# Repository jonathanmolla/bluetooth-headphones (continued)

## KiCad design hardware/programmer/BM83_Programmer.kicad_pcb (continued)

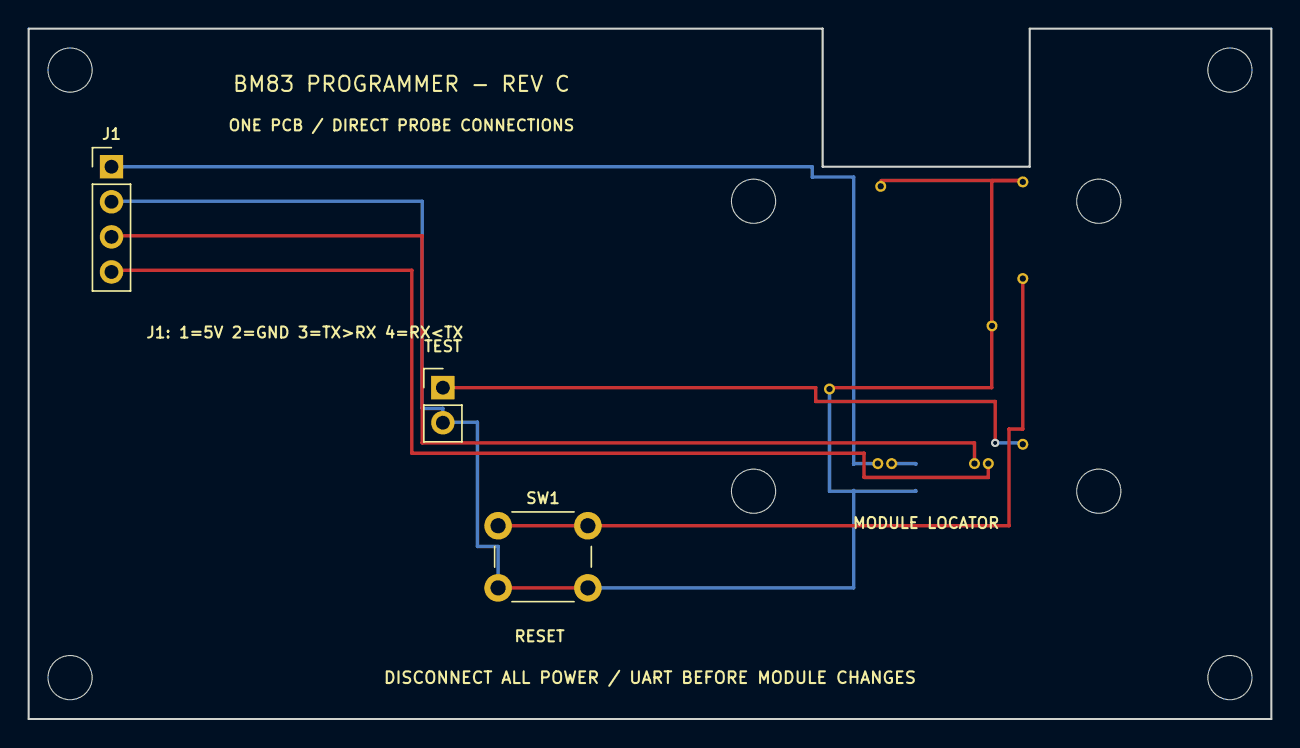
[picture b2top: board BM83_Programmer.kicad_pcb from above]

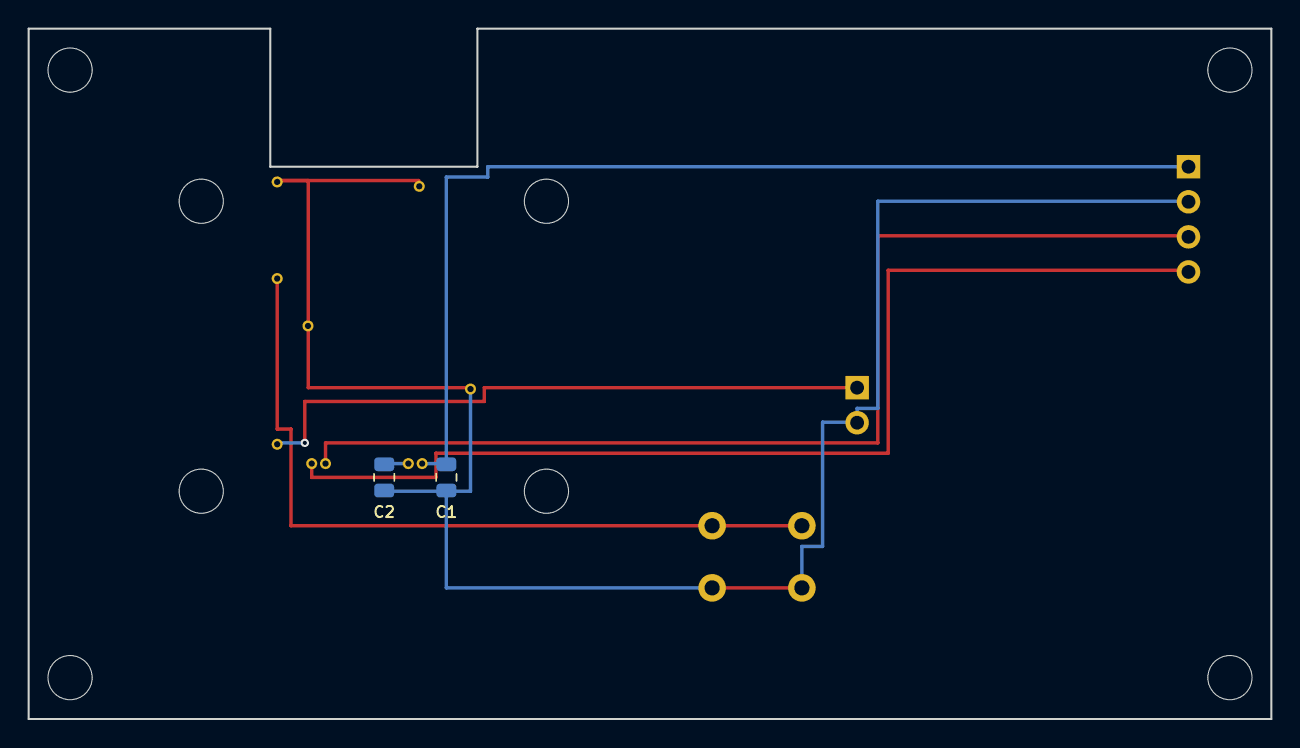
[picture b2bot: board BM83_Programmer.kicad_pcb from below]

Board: 2 copper layers, 90.0 x 50.0 mm, 23 parts (2 on the bottom side), 7 nets.

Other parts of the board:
H1, H2, H3, H4, H5, H6, H7, H8: MountingHole_3.2mm_M3

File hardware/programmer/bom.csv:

Reference,Value,Footprint,Datasheet,Status
C1,1uF / 25V X7R,Capacitor_SMD:C_0805_2012Metric,https://www.murata.com/en-us/products/productdetail?partno=G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,Saved schematic value; see review for pending recommendations
C2,1uF / 25V X7R,Capacitor_SMD:C_0805_2012Metric,https://www.murata.com/en-us/products/productdetail?partno=G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,Saved schematic value; see review for pending recommendations
J1,USB-UART 3V3 LOGIC,Connector_PinHeader_2.54mm:PinHeader_1x04_P2.54mm_Vertical,https://www.samtec.com/products/tsw-104-07-g-s,Saved schematic value; see review for pending recommendations
JP2,TEST MODE,Connector_PinHeader_2.54mm:PinHeader_1x02_P2.54mm_Vertical,https://www.samtec.com/products/tsw-102-07-g-s,Saved schematic value; see review for pending recommendations
P1,BM83 PAD 22,BM83_Programmer:TestPoint_INGUN_GKS080_SolderTail,https://ingun.com/media/01/86/fe/1752238559/INGUN_GKS-080_30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,Saved schematic value; see review for pending recommendations
P2,BM83 PAD 23,BM83_Programmer:TestPoint_INGUN_GKS080_SolderTail,https://ingun.com/media/01/86/fe/1752238559/INGUN_GKS-080_30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,Saved schematic value; see review for pending recommendations
P3,BM83 PAD 29,BM83_Programmer:TestPoint_INGUN_GKS080_SolderTail,https://ingun.com/media/01/86/fe/1752238559/INGUN_GKS-080_30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,Saved schematic value; see review for pending recommendations
P4,BM83 PAD 30,BM83_Programmer:TestPoint_INGUN_GKS080_SolderTail,https://ingun.com/media/01/86/fe/1752238559/INGUN_GKS-080_30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,Saved schematic value; see review for pending recommendations
P5,BM83 PAD 31,BM83_Programmer:TestPoint_INGUN_GKS080_SolderTail,https://ingun.com/media/01/86/fe/1752238559/INGUN_GKS-080_30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,Saved schematic value; see review for pending recommendations
P6,BM83 PAD 43,BM83_Programmer:TestPoint_INGUN_GKS080_SolderTail,https://ingun.com/media/01/86/fe/1752238559/INGUN_GKS-080_30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,Saved schematic value; see review for pending recommendations
P7,BM83 PAD 16,BM83_Programmer:TestPoint_INGUN_GKS080_SolderTail,https://ingun.com/media/01/86/fe/1752238559/INGUN_GKS-080_30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,Saved schematic value; see review for pending recommendations
P8,BM83 PAD 50,BM83_Programmer:TestPoint_INGUN_GKS080_SolderTail,https://ingun.com/media/01/86/fe/1752238559/INGUN_GKS-080_30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,Saved schematic value; see review for pending recommendations
P9,BM83 PAD 56,BM83_Programmer:TestPoint_INGUN_GKS080_SolderTail,https://ingun.com/media/01/86/fe/1752238559/INGUN_GKS-080_30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,Saved schematic value; see review for pending recommendations
P10,BM83 PAD 57,BM83_Programmer:TestPoint_INGUN_GKS080_SolderTail,https://ingun.com/media/01/86/fe/1752238559/INGUN_GKS-080_30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,Saved schematic value; see review for pending recommendations
SW1,RESET,Button_Switch_THT:SW_PUSH_6mm,https://omronfs.omron.com/en_US/ecb/products/pdf/en-b3f.pdf,Saved schematic value; see review for pending recommendations

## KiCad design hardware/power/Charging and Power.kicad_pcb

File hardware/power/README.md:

# Charging and power board

This board contains the USB power input, MCP73833 battery-charging circuit, and TPS7A2030PDBVR 3.0 V regulator.

## Charging and power PCB

**Editable board layout:** [Charging and Power.kicad_pcb](Charging%20and%20Power.kicad_pcb)

**Open the complete KiCad project:** [Charging and Power.kicad_pro](Charging%20and%20Power.kicad_pro)

**View the layout in your browser:** [Charging and power PCB preview](../../docs/images/power-board.svg)

## Schematic and component list

| File | Contents |
| --- | --- |
| [Power schematic](Charging%20and%20Power.kicad_sch) | Charging, regulation, indicators and board connections |
| [Component list](bom.csv) | Schematic references, values, footprints and datasheet links |

[View the power schematic](../../docs/schematics/power/Charging%20and%20Power.svg) · [Open the main audio board](../main/)

## Library files

`MCP73833-AMI_UN.pretty/` and `TPS7A2030PDBVR.pretty/` contain the local charger and regulator CAD assets. Keep these folders and both library tables beside the project when downloading it.

## November 14 review

[Cross-board circuit and layout review](../../docs/design-review-2026-11-14.md) records component values, inter-board pinout, battery/driver selection and reference-design comparisons. The CSV lists schematic parts; the existing Google document remains the purchasing BOM.

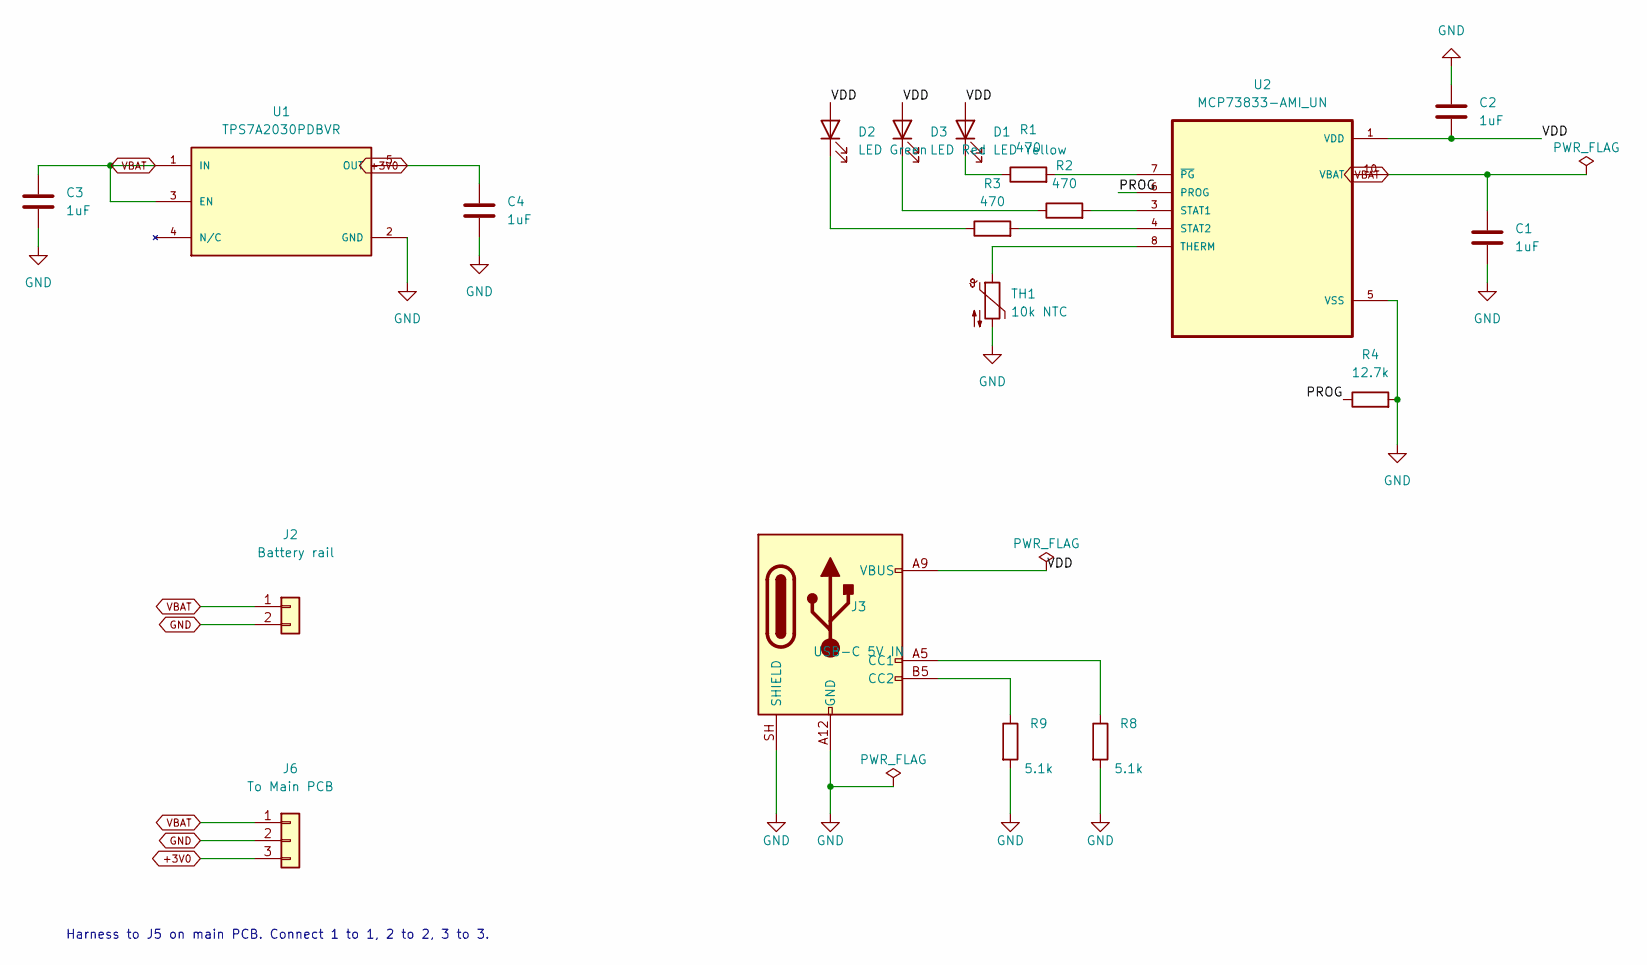
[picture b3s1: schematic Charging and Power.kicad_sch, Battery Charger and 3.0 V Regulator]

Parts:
C1, C2, C3, C4: 1uF; C_0805_2012Metric; MPN GRM219R71E105KA88D
D1: LED Yellow; LED_0805_2012Metric; MPN AP2012SYC
D2: LED Green; LED_0805_2012Metric; MPN AP2012SGC
D3: LED Red; LED_0805_2012Metric; MPN APT2012SURCK
J2: Battery rail; JST_PH_B2B-PH-K_1x02_P2.00mm_Vertical; MPN B2B-PH-K-S(LF)(SN)
J3: USB-C 5V IN; USB_C_Receptacle_GCT_USB4125-xx-x_6P_TopMnt_Horizontal; MPN USB4125-GF-A
J6: To Main PCB; JST_PH_B3B-PH-K_1x03_P2.00mm_Vertical; MPN B3B-PH-K-S(LF)(SN)
R1, R2, R3: 470; R_0805_2012Metric; MPN ERJ-6ENF4700V
R4: 12.7k; R_0603_1608Metric; MPN RC0603FR-0712K7L
R8, R9: 5.1k; R_0805_2012Metric; MPN RC0805FR-075K1L
TH1: 10k NTC; SolderWire-0.1sqmm_1x02_P3.6mm_D0.4mm_OD1mm; MPN B57861S0103F040
U1: TPS7A2030PDBVR; SOT95P280X145-5N; PARTREV H
U2: MCP73833-AMI_UN; SOP50P490X110-10N

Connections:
+3V0: C4.1, J6.3, U1.5 (OUT)
/PROG: R4.1, U2.6 (PROG)
GND: C1.2, C2.1, C3.2, C4.2, J2.2, J3.A12 (GND), J3.B12 (GND), J3.SH (SHIELD), J6.2, R4.2, R8.2, R9.2, TH1.2, U1.2 (GND), U2.5 (VSS)
unnamed: D1.1 (K), R1.1
unnamed: D2.1 (K), R3.1
unnamed: D3.1 (K), R2.1
unnamed: J3.A5 (CC1), R8.1
unnamed: J3.B5 (CC2), R9.1
unnamed: R2.2, U2.3 (STAT1)
unnamed: R3.2, U2.4 (STAT2)
unnamed: TH1.1, U2.8 (THERM)
unnamed: R1.2, U2.7 (~PG)
VBAT: C1.1, C3.1, J2.1, J6.1, U1.1 (IN), U1.3 (EN), U2.9 (VBAT), U2.10 (VBAT)
VDD: C2.2, D1.2 (A), D2.2 (A), D3.2 (A), J3.A9 (VBUS), J3.B9 (VBUS), U2.1 (VDD), U2.2 (VDD)

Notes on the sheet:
Harness to J5 on main PCB. Connect 1 to 1, 2 to 2, 3 to 3.

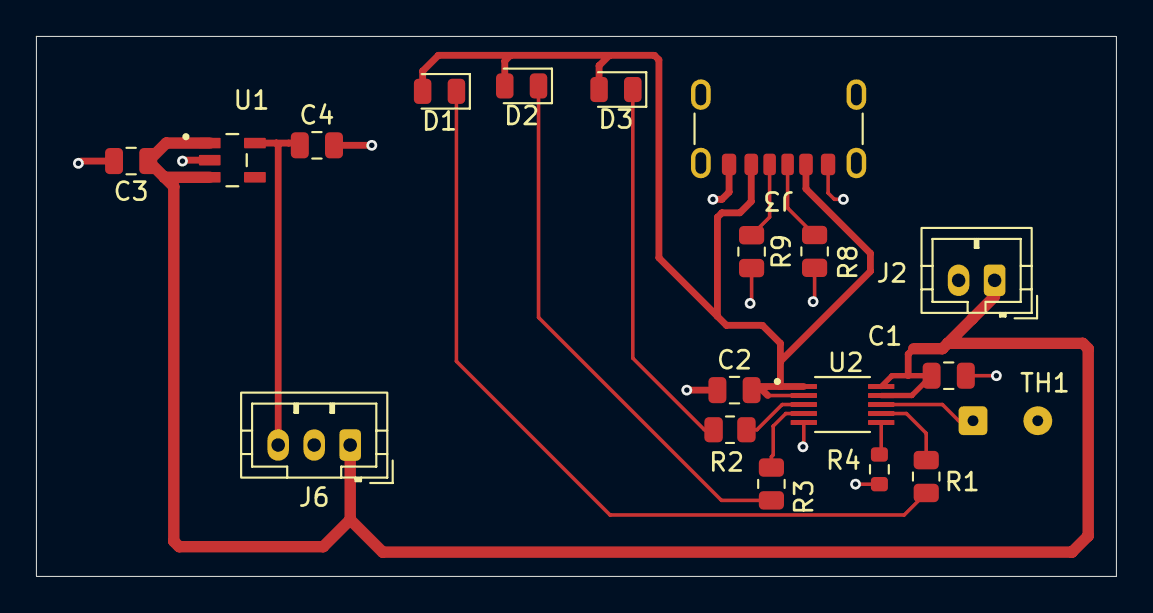
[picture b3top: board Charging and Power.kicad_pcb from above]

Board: 2 copper layers, 60.0 x 30.0 mm, 19 parts (0 on the bottom side), 14 nets.

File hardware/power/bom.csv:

Reference,Value,Footprint,Datasheet,Status
C1,1uF,Capacitor_SMD:C_0805_2012Metric,,Schematic-derived; verify before purchasing
C2,1uF,Capacitor_SMD:C_0805_2012Metric,,Schematic-derived; verify before purchasing
C3,1uF,Capacitor_SMD:C_0805_2012Metric,,Schematic-derived; verify before purchasing
C4,1uF,Capacitor_SMD:C_0805_2012Metric,,Schematic-derived; verify before purchasing
D1,LED Yellow,LED_SMD:LED_0805_2012Metric,,Schematic-derived; verify before purchasing
D2,LED Green,LED_SMD:LED_0805_2012Metric,,Schematic-derived; verify before purchasing
D3,LED Red,LED_SMD:LED_0805_2012Metric,,Schematic-derived; verify before purchasing
J2,Battery rail,Connector_JST:JST_PH_B2B-PH-K_1x02_P2.00mm_Vertical,,Schematic-derived; verify before purchasing
J3,USB-C 5V IN,Connector_USB:USB_C_Receptacle_GCT_USB4125-xx-x_6P_TopMnt_Horizontal,,Schematic-derived; verify before purchasing
J6,To Main PCB,Connector_JST:JST_PH_B3B-PH-K_1x03_P2.00mm_Vertical,,Schematic-derived; verify before purchasing
R1,470,Resistor_SMD:R_0805_2012Metric,,Schematic-derived; verify before purchasing
R2,470,Resistor_SMD:R_0805_2012Metric,,Schematic-derived; verify before purchasing
R3,470,Resistor_SMD:R_0805_2012Metric,,Schematic-derived; verify before purchasing
R4,12.7k,Resistor_SMD:R_0603_1608Metric,,Schematic-derived; verify before purchasing
R8,5.1k,Resistor_SMD:R_0805_2012Metric,,Schematic-derived; verify before purchasing
R9,5.1k,Resistor_SMD:R_0805_2012Metric,,Schematic-derived; verify before purchasing
TH1,10k NTC,Connector_Wire:SolderWire-0.1sqmm_1x02_P3.6mm_D0.4mm_OD1mm,,Schematic-derived; verify before purchasing
U1,TPS7A2030PDBVR,TPS7A2030PDBVR:SOT95P280X145-5N,,Schematic-derived; verify before purchasing
U2,MCP73833-AMI_UN,MCP73833-AMI_UN:SOP50P490X110-10N,,Schematic-derived; verify before purchasing

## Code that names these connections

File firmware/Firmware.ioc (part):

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Mcu.Name=STM32U031C8Tx
Mcu.Package=LQFP48
Mcu.UserName=STM32U031C8Tx
PA0.GPIOParameters=GPIO_PuPd,GPIO_Label
PA0.GPIO_Label=BTN_VOL_UP
PA0.GPIO_PuPd=GPIO_PULLUP
PA0.Signal=GPIO_Input
PA1.GPIOParameters=GPIO_PuPd,GPIO_Label
PA1.GPIO_Label=BTN_VOL_DOWN
PA1.GPIO_PuPd=GPIO_PULLUP
PA1.Signal=GPIO_Input
PA10.Mode=Asynchronous
PA10.Signal=USART1_RX
PA13\ (SWDIO).Mode=Serial_Wire
PA13\ (SWDIO).Signal=DEBUG_JTMS-SWDIO
PA14\ (SWCLK).Mode=Serial_Wire
PA14\ (SWCLK).Signal=DEBUG_JTCK-SWCLK
PA2.GPIOParameters=GPIO_PuPd,GPIO_Label
PA2.GPIO_Label=BTN_PLAY_PAUSE
PA2.GPIO_PuPd=GPIO_PULLUP
PA2.Signal=GPIO_Input
PA3.GPIOParameters=GPIO_Label
PA3.GPIO_Label=AMP_ENABLE
PA3.Signal=GPIO_Output
PA4.GPIOParameters=PinState,GPIO_PuPd,GPIO_Label,GPIO_ModeDefaultOutputPP
PA4.GPIO_Label=BT_RESET
PA4.GPIO_ModeDefaultOutputPP=GPIO_MODE_OUTPUT_OD
PA4.GPIO_PuPd=GPIO_NOPULL
PA4.PinState=GPIO_PIN_SET
PA4.Signal=GPIO_Output
PA5.GPIOParameters=GPIO_Label
PA5.GPIO_Label=BT_WAKE
PA5.Signal=GPIO_Output
PA6.GPIOParameters=GPIO_Label
PA6.GPIO_Label=BT_WAKE_IND
PA6.Signal=GPIO_Input
PA7.GPIOParameters=GPIO_Label
PA7.GPIO_Label=BAT_SENSE
PA7.Mode=IN14
PA7.Signal=ADC1_IN14
PA9.Mode=Asynchronous
PA9.Signal=USART1_TX
PB13.GPIOParameters=GPIO_PuPd,GPIO_Label
PB13.GPIO_Label=CHARGING_IND
PB13.GPIO_PuPd=GPIO_NOPULL
PB13.Signal=GPIO_Input
PB6.Mode=I2C
PB6.Signal=I2C1_SCL
PB7.Mode=I2C
PB7.Signal=I2C1_SDA
RCC.HSE_VALUE=4000000
RCC.SYSCLKFreq_VALUE=16000000
board=custom
